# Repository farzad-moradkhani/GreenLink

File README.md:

[English](README.md) | [Deutsch](README.de.md)

# Green Link 🌱

**Smart Dual-Zone IoT Garden Watering System**

Green Link is an open-source, autonomous IoT irrigation system designed for efficient and precise garden watering. It combines reliable ESP32-based hardware with a modern Android application, enabling both scheduled autonomous operation and convenient remote control via WiFi.
---
## 🟢 Updates

Designed Motor Channel module and also added it's 3D components

---

## ✨ Key Features

- **Two independent watering channels** with individual control
- **PWM-based flow control** for precise watering intensity
- **Sensor integration**:
  - Capacitive soil moisture sensors (one per zone)
  - Water tank level sensor
- **DS3231 Real-Time Clock (RTC)** for accurate time-based scheduling
- **Autonomous operation** – works independently of the mobile app
- **Local WiFi communication** – no cloud service required
- **Buzzer alerts** for low water level and system notifications
- **Modern Android App** with clean Jetpack Compose UI

---

## 🛠️ Tech Stack

### Hardware & Firmware
- **Microcontroller**: ESP32
- **Framework**: PlatformIO + C++
- **Communication**: JSON over HTTP (AsyncWebServer)
- **Storage**: LittleFS + Preferences
- **Sensors & Actuators**: Soil moisture, ultrasonic/float level, PWM pumps, buzzer, DS3231 RTC

### Android Application
- **Language**: Kotlin
- **UI**: Jetpack Compose + Material 3
- **Architecture**: MVVM + Repository Pattern
- **Networking**: Ktor Client (or Retrofit)
- **Dependency Injection**: Hilt

---

## 📱 Android App Features

- Real-time sensor dashboard (humidity + water level)
- Manual pump control with PWM flow sliders
- Advanced scheduling system (per channel, recurring)
- WiFi device connection and discovery
- Responsive and intuitive user interface

---

## 📂 Project Structure

- `/firmware` – ESP32 source code
- `/android` – Jetpack Compose Android app
- `/hardware` – Schematics, BOM, and 3D models
- `/docs` – Detailed documentation and API specification

---

## 🚀 Getting Started

### Prerequisites
- ESP32 development board
- Two 12V water pumps
- Soil moisture sensors + water level sensor
- DS3231 RTC module
- Android device (API 24+)

### Firmware Setup
1. Clone the repository
2. Open the `firmware` folder in PlatformIO
3. Configure WiFi credentials in `config.h`
4. Build and flash to ESP32

### Android App Setup
1. Open the `android` folder in Android Studio
2. Connect to the same WiFi network as the device
3. Enter device IP or use discovery feature

Detailed setup instructions are available in the [docs](/docs) folder.

---

## 📸 Screenshots

*(Add screenshots here: Dashboard, Schedule screen, Manual control, Hardware photo)*

---

## 🎯 Project Goals

This project showcases full-stack IoT development skills, including embedded systems programming, hardware integration, sensor-actuator control, and modern mobile application development. It is built with clean code, modularity, and reliability in mind.

Ideal for learning or as a practical demonstration of embedded + mobile engineering capabilities.

---

## 📄 License

This project is licensed under the **MIT License** – see the [LICENSE](LICENSE) file for details.

---

## 🤝 Contributing

Contributions are welcome! Please read [CONTRIBUTING.md](CONTRIBUTING.md) for guidelines.

---

**Made with ❤️ by farzad for efficient and sustainable gardening.**

*Project developed as a complete IoT solution for portfolio and learning purposes.*

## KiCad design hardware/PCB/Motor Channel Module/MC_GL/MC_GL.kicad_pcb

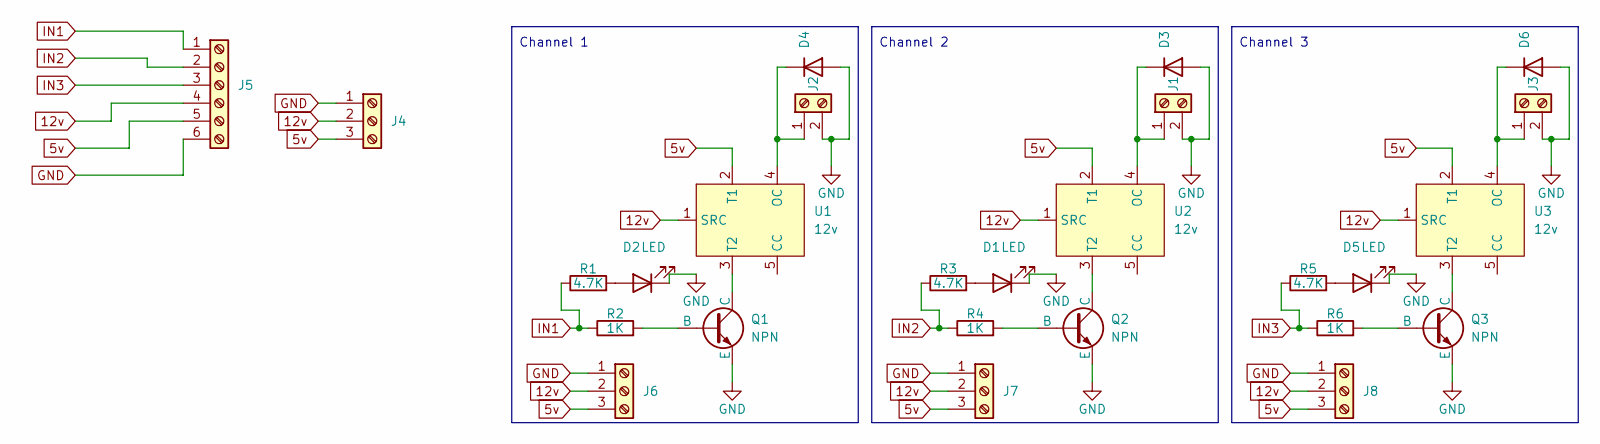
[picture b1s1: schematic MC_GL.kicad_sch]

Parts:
D1, D2, D5: LED; LED_D5.0mm
D3, D4, D6: 1N4002; D_DO-41_SOD81_P10.16mm_Horizontal
J1, J2, J3: S_T_01x02; TerminalBlock_MaiXu_MX126-5.0-02P_1x02_P5.00mm
J4, J6, J7, J8: Screw_Terminal_01x03; TerminalBlock_MaiXu_MX126-5.0-03P_1x03_P5.00mm
J5: Screw_Terminal_01x06; TerminalBlock_MaiXu_MX126-5.0-06P_1x06_P5.00mm
Q1, Q2, Q3: NPN; 2N2222
R1, R3, R5: 4.7K; R_Axial_DIN0309_L9.0mm_D3.2mm_P20.32mm_Horizontal
R2, R4, R6: 1K; R_Axial_DIN0309_L9.0mm_D3.2mm_P20.32mm_Horizontal
U1, U2, U3: 12v; HJR-3FF-S-Z

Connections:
5v: J4.3, J5.5, J6.3, J7.3, J8.3, U1.2 (T1), U2.2 (T1), U3.2 (T1)
12v: J4.2, J5.4, J6.2, J7.2, J8.2, U1.1 (SRC), U2.1 (SRC), U3.1 (SRC)
GND: D1.1 (K), D2.1 (K), D3.2 (A), D4.2 (A), D5.1 (K), D6.2 (A), J1.2, J2.2, J3.2, J4.1, J5.6, J6.1, J7.1, J8.1, Q1.3 (E), Q2.3 (E), Q3.3 (E)
IN1: J5.1, R1.1, R2.1
IN2: J5.2, R3.1, R4.1
IN3: J5.3, R5.1, R6.1
unnamed: D1.2 (A), R3.2
unnamed: D2.2 (A), R1.2
unnamed: D3.1 (K), J1.1, U2.4 (OC)
unnamed: D4.1 (K), J2.1, U1.4 (OC)
unnamed: D5.2 (A), R5.2
unnamed: D6.1 (K), J3.1, U3.4 (OC)
unnamed: Q1.2 (B), R2.2
unnamed: Q1.1 (C), U1.3 (T2)
unnamed: Q2.2 (B), R4.2
unnamed: Q2.1 (C), U2.3 (T2)
unnamed: Q3.2 (B), R6.2
unnamed: Q3.1 (C), U3.3 (T2)

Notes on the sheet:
Channel 1
Channel 3
Channel 2

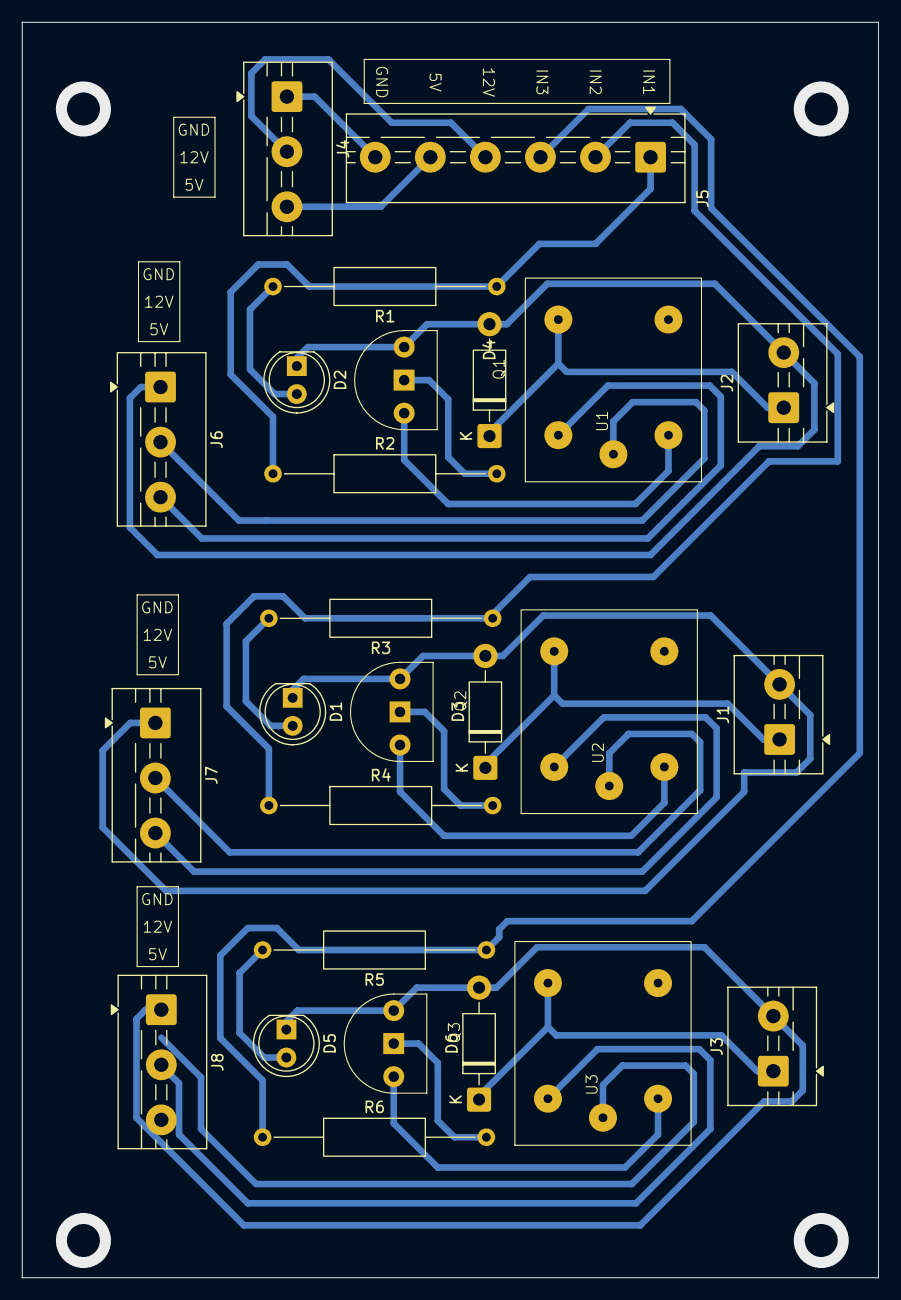
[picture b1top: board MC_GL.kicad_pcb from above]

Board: 2 copper layers, 77.7 x 114.0 mm, 26 parts (0 on the bottom side), 18 nets.

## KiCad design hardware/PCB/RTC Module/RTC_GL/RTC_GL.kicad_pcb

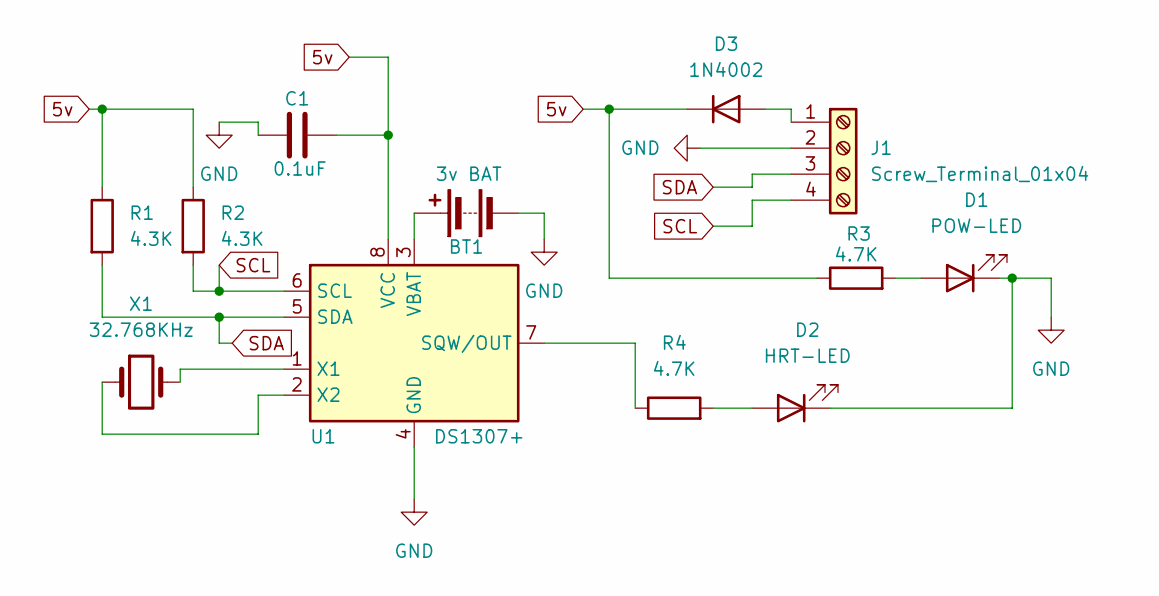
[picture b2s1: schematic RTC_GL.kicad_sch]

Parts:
BT1: 3v BAT; BatteryHolder_MYOUNG_BS-07-A1BJ001_CR2032
C1: 0.1uF; C_Disc_D6.0mm_W2.5mm_P5.00mm
D1: POW-LED; LED_D3.0mm
D2: HRT-LED; LED_D3.0mm
D3: 1N4002; D_DO-41_SOD81_P10.16mm_Horizontal
J1: Screw_Terminal_01x04; TerminalBlock_Phoenix_MPT-0,5-4-2.54_1x04_P2.54mm_Horizontal
R1, R2: 4.3K; R_Axial_DIN0309_L9.0mm_D3.2mm_P20.32mm_Horizontal
R3, R4: 4.7K; R_Axial_DIN0309_L9.0mm_D3.2mm_P20.32mm_Horizontal
U1: DS1307+; DIP-8_W7.62mm
X1: 32.768KHz; Crystal_C38-LF_D3.0mm_L8.0mm_Horizontal

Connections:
5v: C1.2, D3.1 (K), R1.1, R2.1, R3.1, U1.8 (VCC)
GND: BT1.2 (-), C1.1, D1.1 (K), D2.1 (K), J1.2, U1.4 (GND)
unnamed: BT1.1 (+), U1.3 (VBAT)
unnamed: D1.2 (A), R3.2
unnamed: D2.2 (A), R4.2
unnamed: D3.2 (A), J1.1
unnamed: R4.1, U1.7 (SQW/OUT)
unnamed: U1.1 (X1), X1.2
unnamed: U1.2 (X2), X1.1
SCL: J1.4, R2.2, U1.6 (SCL)
SDA: J1.3, R1.2, U1.5 (SDA)

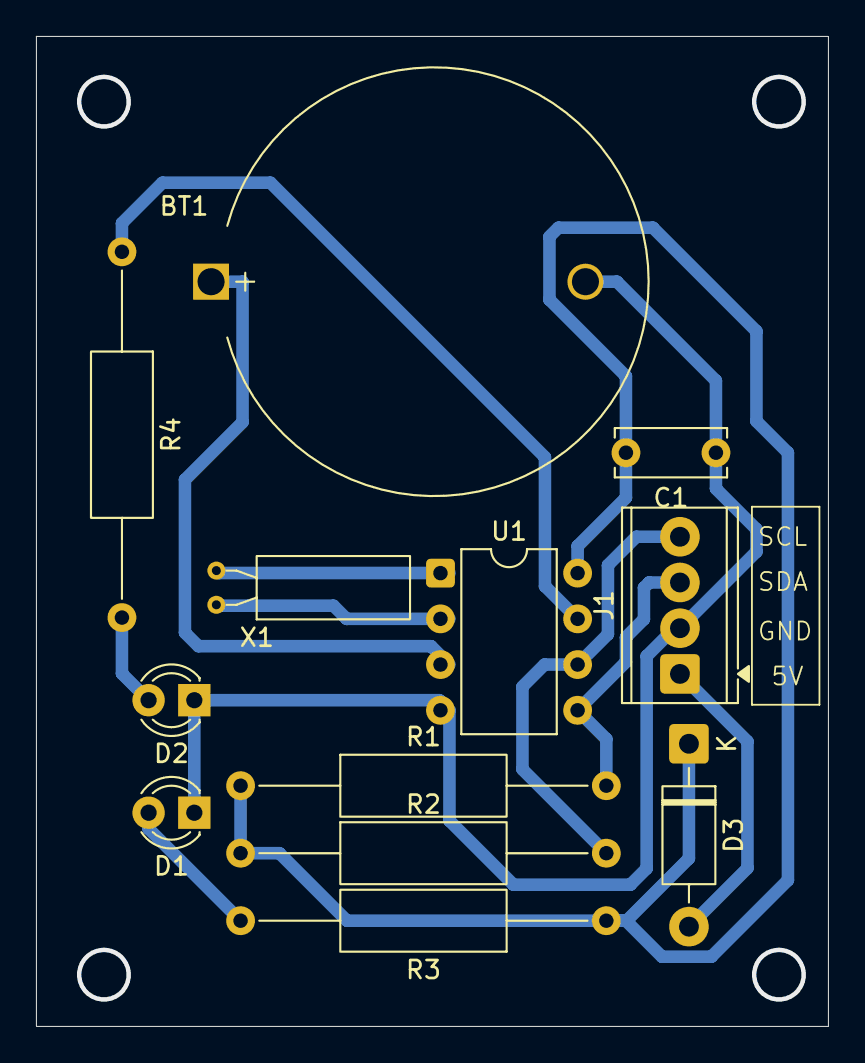
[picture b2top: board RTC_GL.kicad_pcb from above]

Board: 2 copper layers, 44.0 x 55.0 mm, 12 parts (0 on the bottom side), 11 nets.

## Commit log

2026-05-31 Created project structure
2026-06-01 Added 3D models to pcb of RTC (real time clock) module.
2026-06-02 Designed Motor Channel module and also added it's 3D components

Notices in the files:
README.md:
License: MIT
